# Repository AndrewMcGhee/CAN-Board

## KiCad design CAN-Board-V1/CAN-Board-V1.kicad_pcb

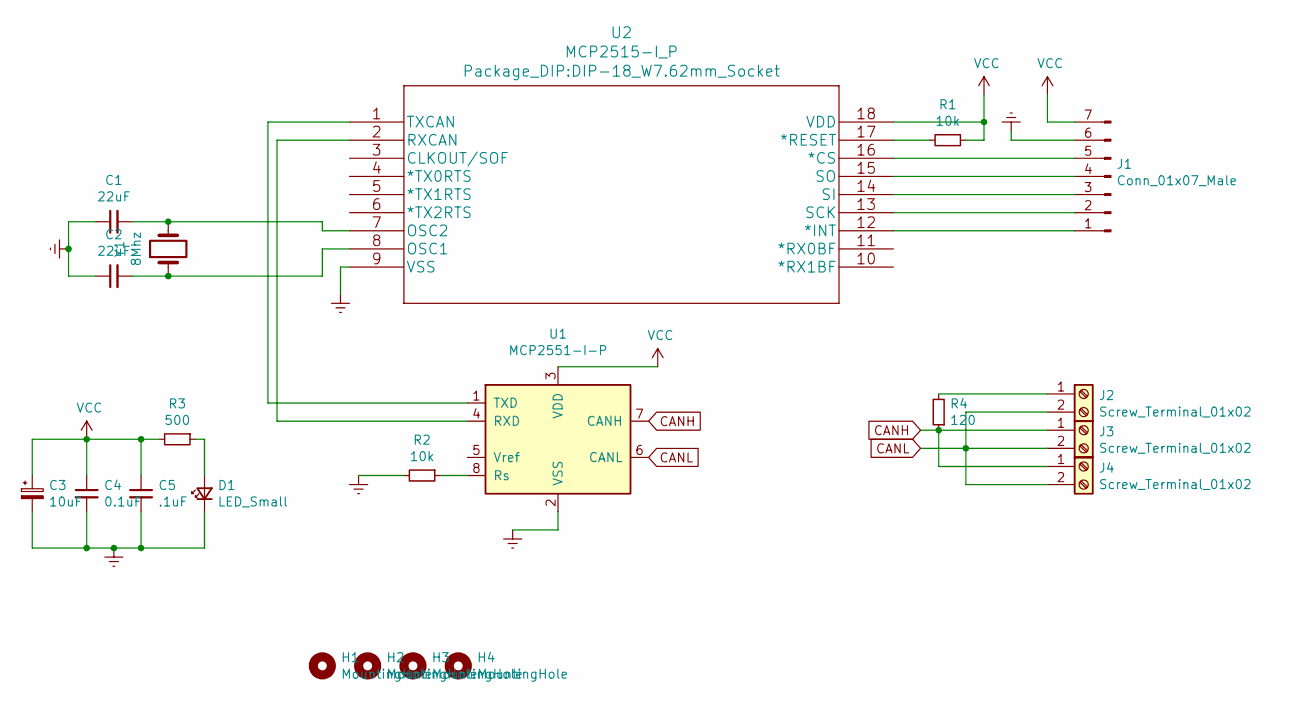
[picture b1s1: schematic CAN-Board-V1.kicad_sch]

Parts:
C1, C2: 22uF; C_Disc_D5.0mm_W2.5mm_P2.50mm
C3: 10uF; C_Disc_D5.0mm_W2.5mm_P2.50mm
C4: 0.1uF; C_Disc_D5.0mm_W2.5mm_P2.50mm
C5: .1uF; C_Disc_D5.0mm_W2.5mm_P2.50mm
D1: LED_Small; LED_D5.0mm
H1, H2, H3, H4: MountingHole; MountingHole_3.2mm_M3
J1: Conn_01x07_Male; PinHeader_1x07_P2.00mm_Vertical
J2, J3, J4: Screw_Terminal_01x02; TerminalBlock_TE_282834-2_1x02_P2.54mm_Horizontal
R1, R2: 10k; R_Axial_DIN0207_L6.3mm_D2.5mm_P10.16mm_Horizontal
R3: 500; R_Axial_DIN0207_L6.3mm_D2.5mm_P10.16mm_Horizontal
R4: 120; R_Axial_DIN0207_L6.3mm_D2.5mm_P10.16mm_Horizontal
U1: MCP2551-I-P; DIP-8_W7.62mm_Socket
U2: MCP2515-I_P; DIP-18_W7.62mm_Socket
Y1: 8Mhz; Crystal_HC49-4H_Vertical

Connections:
CANH: J3.1, J4.1, R4.1, U1.7 (CANH)
CANL: J2.2, J3.2, J4.2, U1.6 (CANL)
Earth: C1.1, C2.1, C3.2, C4.2, C5.2, D1.1 (K), J1.6, R2.2, U1.2 (VSS), U2.9 (VSS)
unnamed: D1.2 (A), R3.1
unnamed: J1.1, U2.12 (*INT)
unnamed: J1.2, U2.13 (SCK)
unnamed: J1.3, U2.14 (SI)
unnamed: J1.4, U2.15 (SO)
unnamed: J1.5, U2.16 (*CS)
unnamed: J2.1, R4.2
unnamed: U1.4 (RXD), U2.2 (RXCAN)
unnamed: R2.1, U1.8 (Rs)
unnamed: U1.1 (TXD), U2.1 (TXCAN)
unnamed: R1.2, U2.17 (*RESET)
unnamed: C2.2, U2.8 (OSC1), Y1.1
unnamed: C1.2, U2.7 (OSC2), Y1.2
VCC: C3.1, C4.1, C5.1, J1.7, R1.1, R3.2, U1.3 (VDD), U2.18 (VDD)

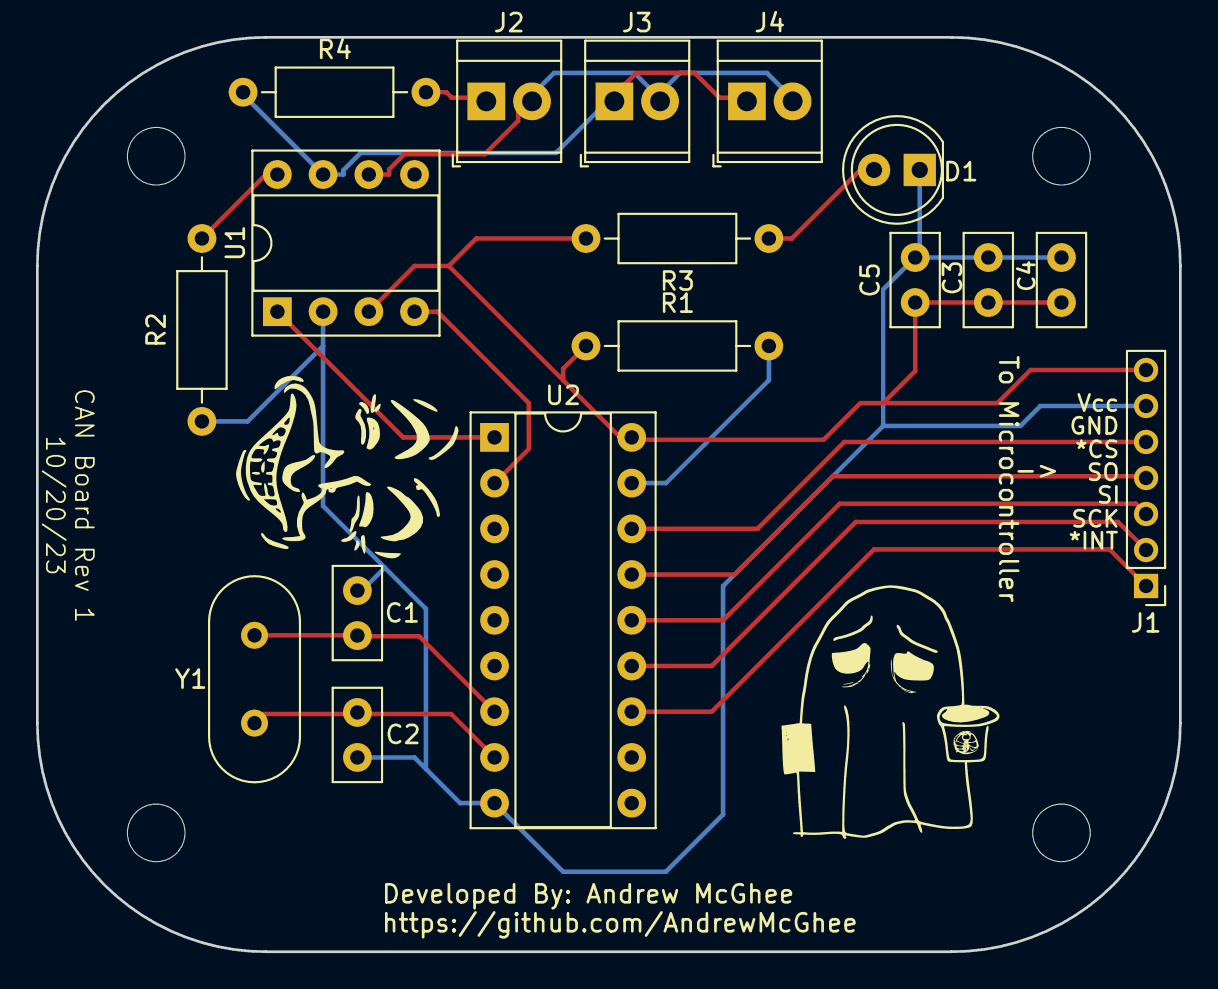
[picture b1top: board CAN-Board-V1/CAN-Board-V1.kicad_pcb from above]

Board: 2 copper layers, 63.5 x 50.8 mm, 21 parts (0 on the bottom side), 17 nets.

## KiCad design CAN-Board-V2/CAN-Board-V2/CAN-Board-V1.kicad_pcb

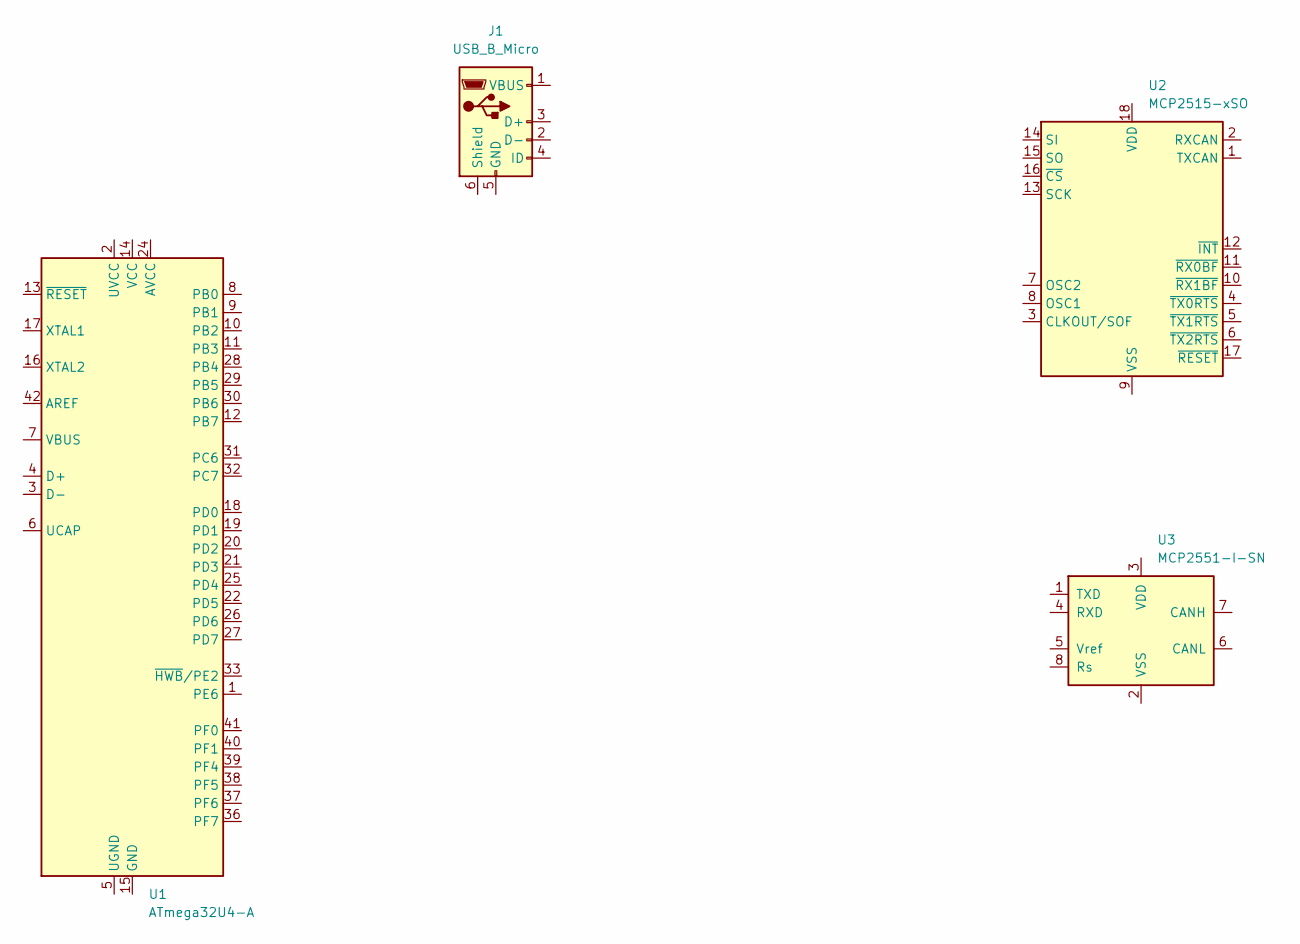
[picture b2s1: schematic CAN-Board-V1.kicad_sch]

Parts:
J1: USB_B_Micro; USB_Micro-B_Molex_47346-0001
U1: ATmega32U4-A; TQFP-44_10x10mm_P0.8mm
U2: MCP2515-xSO; SOIC-18W_7.5x11.6mm_P1.27mm
U3: MCP2551-I-SN; SOIC-8_3.9x4.9mm_P1.27mm

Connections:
unnamed: U1.24 (AVCC), U1.44 (AVCC)
unnamed: U1.15 (GND), U1.23 (GND), U1.35 (GND), U1.43 (GND)
unnamed: U1.14 (VCC), U1.34 (VCC)

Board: 2 copper layers, 4 parts (0 on the bottom side), 3 nets, no tracks yet.

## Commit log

2023-10-18 Added all components and make initial layout
2023-10-23 V1 Complete
2023-10-26 Started on V2
2023-10-26 Fixed
2023-11-01 mian
